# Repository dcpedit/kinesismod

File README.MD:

# Project moved to [Pillz Mod](https://github.com/dcpedit/pillzmod)

This project has been replaced by Pillz Mod: https://github.com/dcpedit/pillzmod

# Kinesis Stapelberg Mod in KiCAD

This is a fork of Aaron Silman's [kinesismod project](https://gitlab.com/Silman/kinesismod.git).  You can read more about it [on his blog](https://silman.io/project/kinesis_mod/)

This fork contains the following changes:

* Created a version that uses the Teensy 4.x
* Created a version that uses the STM32F411 Blackpill controller (`blackpill` directory)
* Use Vial firmware (`firmware` directory).
* Use ZMK firmware (`firmware` directory) wireless PillBug BLE option.

## USB Port

I recommend purchasing the following adapter from Amazon:
https://a.co/d/cRoqHqx

Here's how it looks like after installing:

## Wireless Bluetooth + ZMK
Bluetooth has been verified to work using the PillBug development board.  Below, you can see a 2000mAh 3.7V battery ([Amazon link](https://a.co/d/dVUdHxi)), as well as a 10mm push button ([Amazon link](https://a.co/d/5OVO4dY)) to disconnect the power when needed.

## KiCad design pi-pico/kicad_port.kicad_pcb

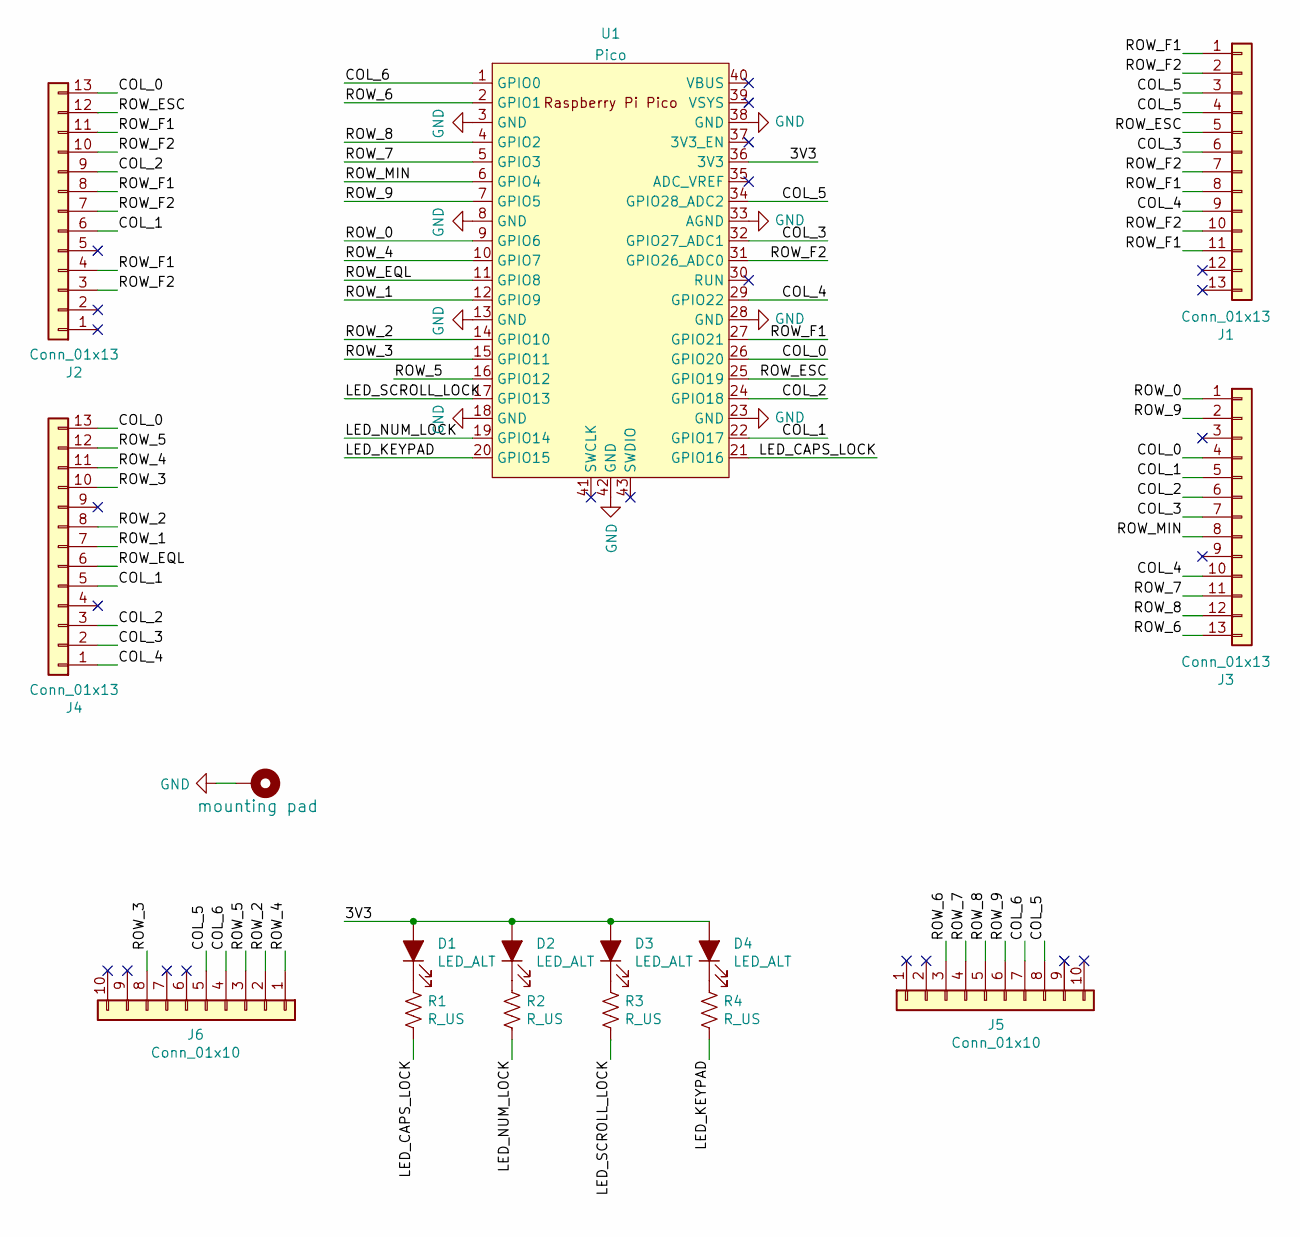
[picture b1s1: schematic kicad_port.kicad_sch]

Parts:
D1, D2, D3, D4: LED_ALT; LED_D3.0mm
H1: mounting pad; MountingHole_4.3mm_M4_Pad
J1, J2: Conn_01x13; Molex_0039532135
J3, J4: Conn_01x13; Molex_039532134
J5, J6: Conn_01x10; Pin_Header_Straight_1x10_Pitch2.54mm
R1, R2, R3, R4: R_US; R_Axial_DIN0204_L3.6mm_D1.6mm_P5.08mm_Horizontal
U1: Pico; RPi_Pico_SMD_TH

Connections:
/3V3: D1.2 (A), D2.2 (A), D3.2 (A), D4.2 (A), U1.36 (3V3)
/COL_0: J2.13, J3.4, J4.13, U1.26 (GPIO20)
/COL_1: J2.6, J3.5, J4.5, U1.22 (GPIO17)
/COL_2: J2.9, J3.6, J4.3, U1.24 (GPIO18)
/COL_3: J1.6, J3.7, J4.2, U1.32 (GPIO27_ADC1)
/COL_4: J1.9, J3.10, J4.1, U1.29 (GPIO22)
/COL_5: J1.3, J1.4, J5.8, J6.5, U1.34 (GPIO28_ADC2)
/COL_6: J5.7, J6.4, U1.1 (GPIO0)
/LED_CAPS_LOCK: R1.2, U1.21 (GPIO16)
/LED_KEYPAD: R4.2, U1.20 (GPIO15)
/LED_NUM_LOCK: R2.2, U1.19 (GPIO14)
/LED_SCROLL_LOCK: R3.2, U1.17 (GPIO13)
/ROW_0: J3.1, U1.9 (GPIO6)
/ROW_1: J4.7, U1.12 (GPIO9)
/ROW_2: J4.8, J6.2, U1.14 (GPIO10)
/ROW_3: J4.10, J6.8, U1.15 (GPIO11)
/ROW_4: J4.11, J6.1, U1.10 (GPIO7)
/ROW_5: J4.12, J6.3, U1.16 (GPIO12)
/ROW_6: J3.13, J5.3, U1.2 (GPIO1)
/ROW_7: J3.11, J5.4, U1.5 (GPIO3)
/ROW_8: J3.12, J5.5, U1.4 (GPIO2)
/ROW_9: J3.2, J5.6, U1.7 (GPIO5)
/ROW_EQL: J4.6, U1.11 (GPIO8)
/ROW_ESC: J1.5, J2.12, U1.25 (GPIO19)
/ROW_F1: J1.1, J1.8, J1.11, J2.4, J2.8, J2.11, U1.27 (GPIO21)
/ROW_F2: J1.2, J1.7, J1.10, J2.3, J2.7, J2.10, U1.31 (GPIO26_ADC0)
/ROW_MIN: J3.8, U1.6 (GPIO4)
GND: H1.1, U1.3 (GND), U1.8 (GND), U1.13 (GND), U1.18 (GND), U1.23 (GND), U1.28 (GND), U1.33 (AGND), U1.38 (GND), U1.42 (GND)
unnamed: D1.1 (K), R1.1
unnamed: D2.1 (K), R2.1
unnamed: D3.1 (K), R3.1
unnamed: D4.1 (K), R4.1

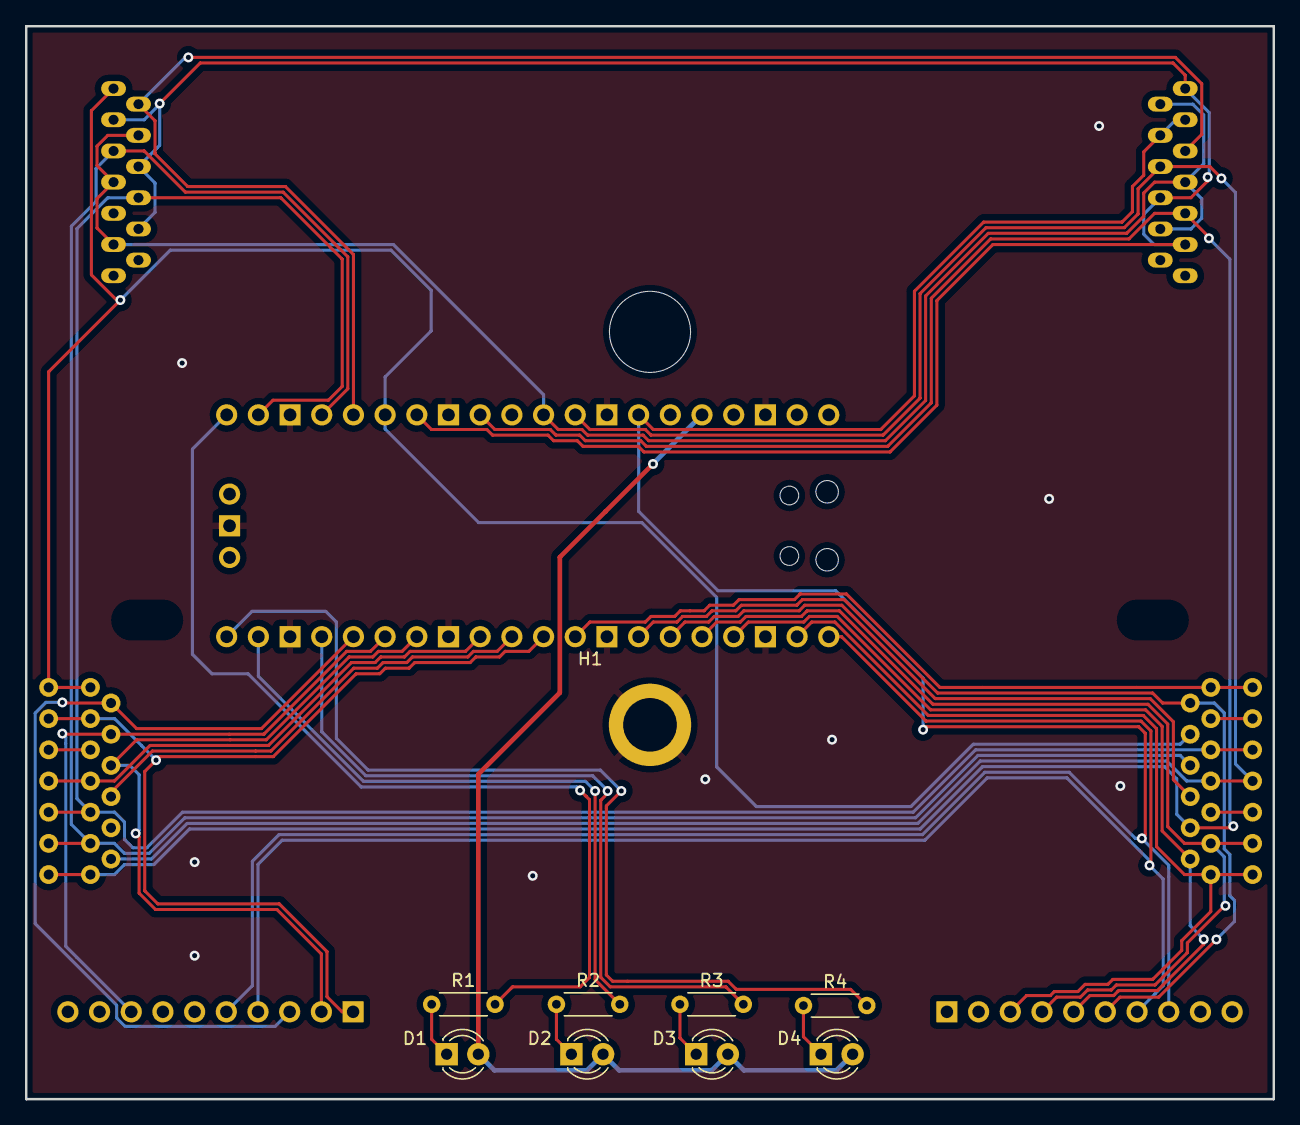
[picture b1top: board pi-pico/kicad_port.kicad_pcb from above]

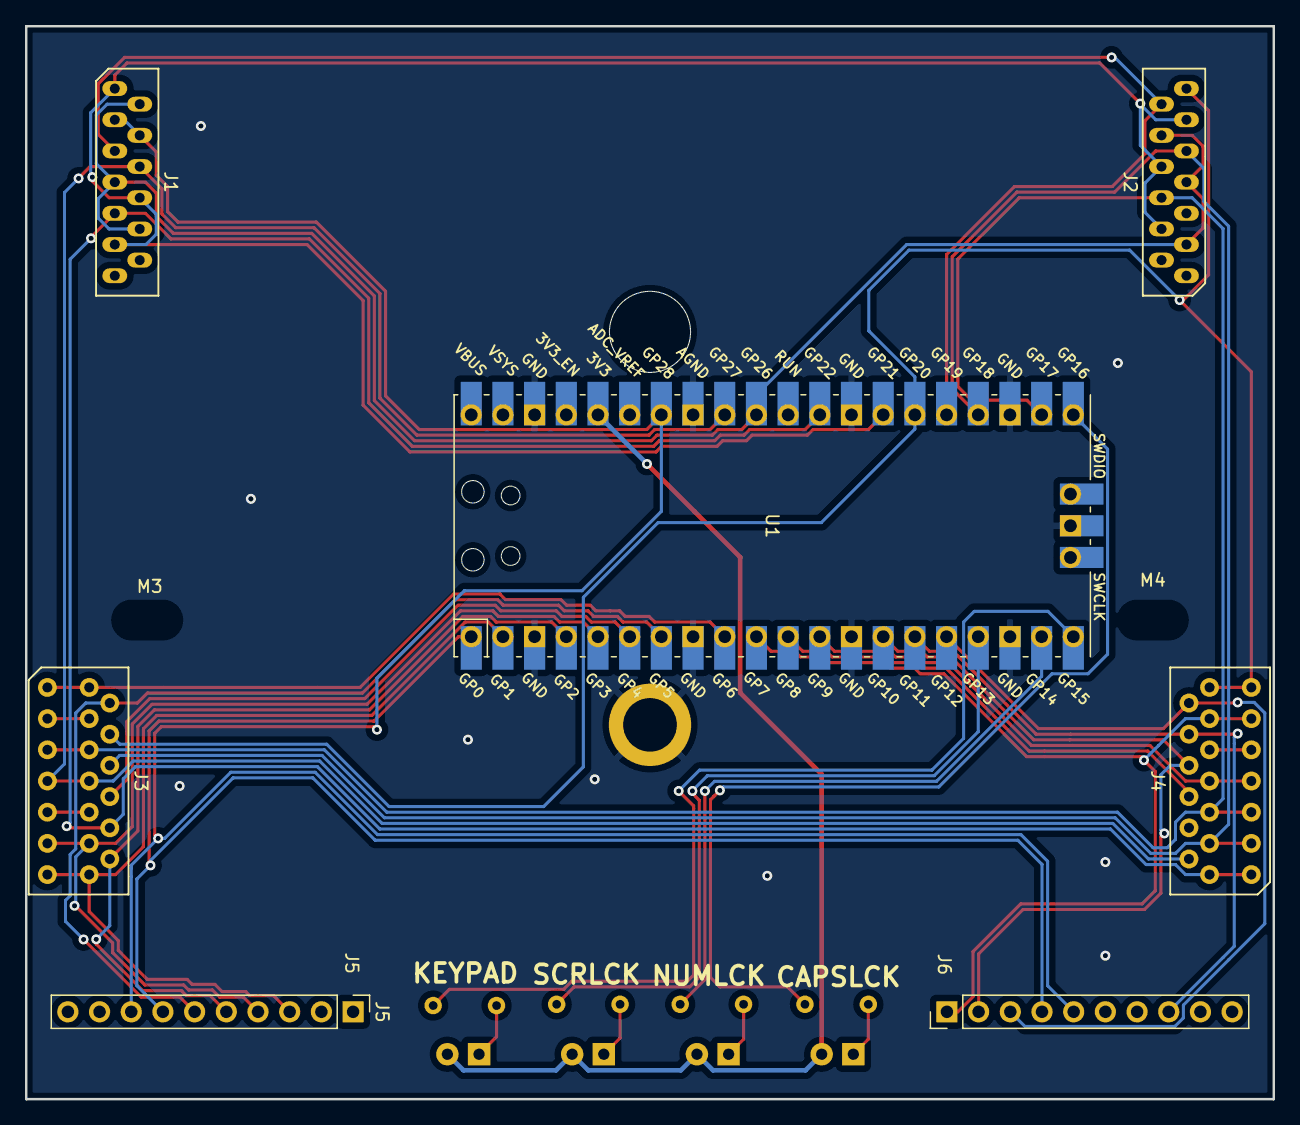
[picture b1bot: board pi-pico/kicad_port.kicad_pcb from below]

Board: 2 copper layers, 100.0 x 86.0 mm, 19 parts (10 on the bottom side), 32 nets.

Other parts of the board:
M1: MountingHole_6.4mm_M6
M3, M4: MountingHole_4.3mm_M4

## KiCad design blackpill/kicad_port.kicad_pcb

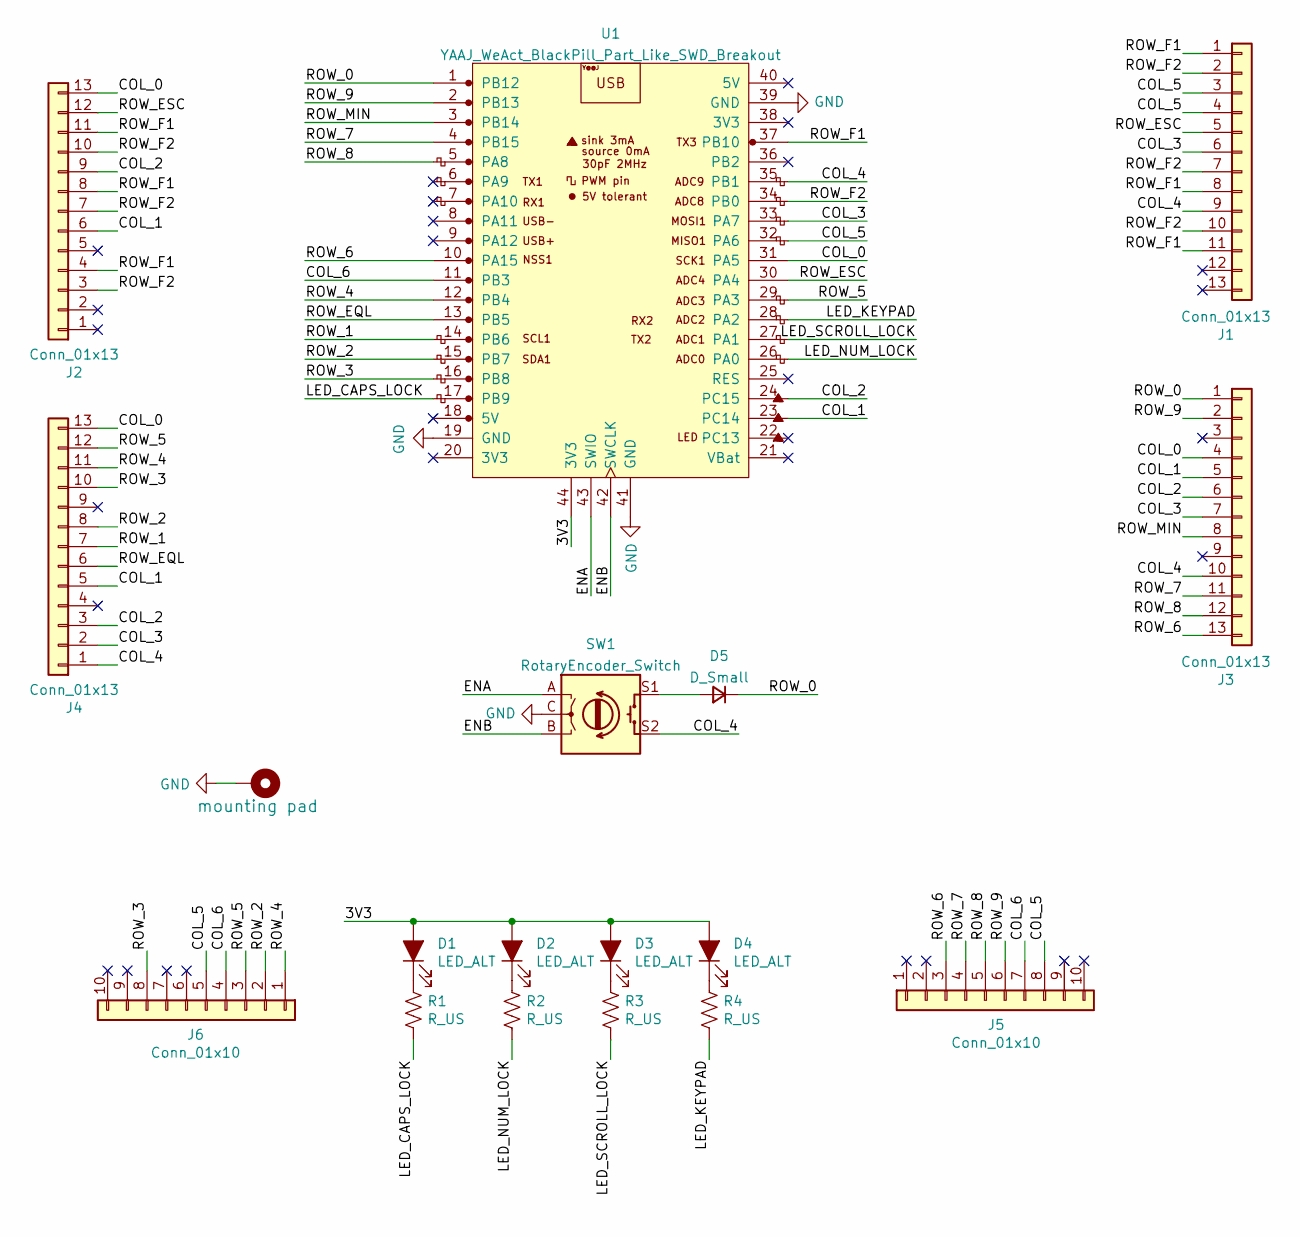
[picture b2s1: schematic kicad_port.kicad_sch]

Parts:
D1, D2, D3, D4: LED_ALT; LED_D3.0mm
D5: D_Small
H1: mounting pad; MountingHole_4.3mm_M4_Pad
J1, J2: Conn_01x13; Molex_0039532135
J3, J4: Conn_01x13; Molex_039532134
J5, J6: Conn_01x10; Pin_Header_Straight_1x10_Pitch2.54mm
R1, R2, R3, R4: R_US; R_Axial_DIN0204_L3.6mm_D1.6mm_P5.08mm_Horizontal
SW1: RotaryEncoder_Switch
U1: YAAJ_WeAct_BlackPill_Part_Like_SWD_Breakout; YAAJ_WeAct_BlackPill_SWD_2

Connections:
/3V3: D1.2 (A), D2.2 (A), D3.2 (A), D4.2 (A), U1.20 (3V3), U1.44 (3V3)
/COL_0: J2.13, J3.4, J4.13, U1.31 (PA5)
/COL_1: J2.6, J3.5, J4.5, U1.23 (PC14)
/COL_2: J2.9, J3.6, J4.3, U1.24 (PC15)
/COL_3: J1.6, J3.7, J4.2, U1.33 (PA7)
/COL_4: J1.9, J3.10, J4.1, SW1.S2, U1.35 (PB1)
/COL_5: J1.3, J1.4, J5.8, J6.5, U1.32 (PA6); also elsewhere on the board
/COL_6: J5.7, J6.4, U1.11 (PB3); also elsewhere on the board
/ENA: SW1.A, U1.43 (SWIO)
/ENB: SW1.B, U1.42 (SWCLK)
/LED_CAPS_LOCK: R1.2, U1.17 (PB9)
/LED_KEYPAD: R4.2, U1.28 (PA2)
/LED_NUM_LOCK: R2.2, U1.26 (PA0)
/LED_SCROLL_LOCK: R3.2, U1.27 (PA1)
/ROW_0: D5.1 (K), J3.1, U1.1 (PB12)
/ROW_1: J4.7, U1.14 (PB6)
/ROW_2: J4.8, J6.2, U1.15 (PB7); also elsewhere on the board
/ROW_3: J4.10, J6.8, U1.16 (PB8); also elsewhere on the board
/ROW_4: J4.11, J6.1, U1.12 (PB4); also elsewhere on the board
/ROW_5: J4.12, J6.3, U1.29 (PA3); also elsewhere on the board
/ROW_6: J3.13, J5.3, U1.10 (PA15); also elsewhere on the board
/ROW_7: J3.11, J5.4, U1.4 (PB15); also elsewhere on the board
/ROW_8: J3.12, J5.5, U1.5 (PA8); also elsewhere on the board
/ROW_9: J3.2, J5.6, U1.2 (PB13); also elsewhere on the board
/ROW_EQL: J4.6, U1.13 (PB5)
/ROW_ESC: J1.5, J2.12, U1.30 (PA4)
/ROW_F1: J1.1, J1.8, J1.11, J2.4, J2.8, J2.11, U1.37 (PB10)
/ROW_F2: J1.2, J1.7, J1.10, J2.3, J2.7, J2.10, U1.34 (PB0)
/ROW_MIN: J3.8, U1.3 (PB14)
GND: H1.1, SW1.C, U1.19 (GND), U1.39 (GND), U1.41 (GND)
unnamed: D1.1 (K), R1.1
unnamed: D2.1 (K), R2.1
unnamed: D3.1 (K), R3.1
unnamed: D4.1 (K), R4.1
unnamed: D5.2 (A), SW1.S1

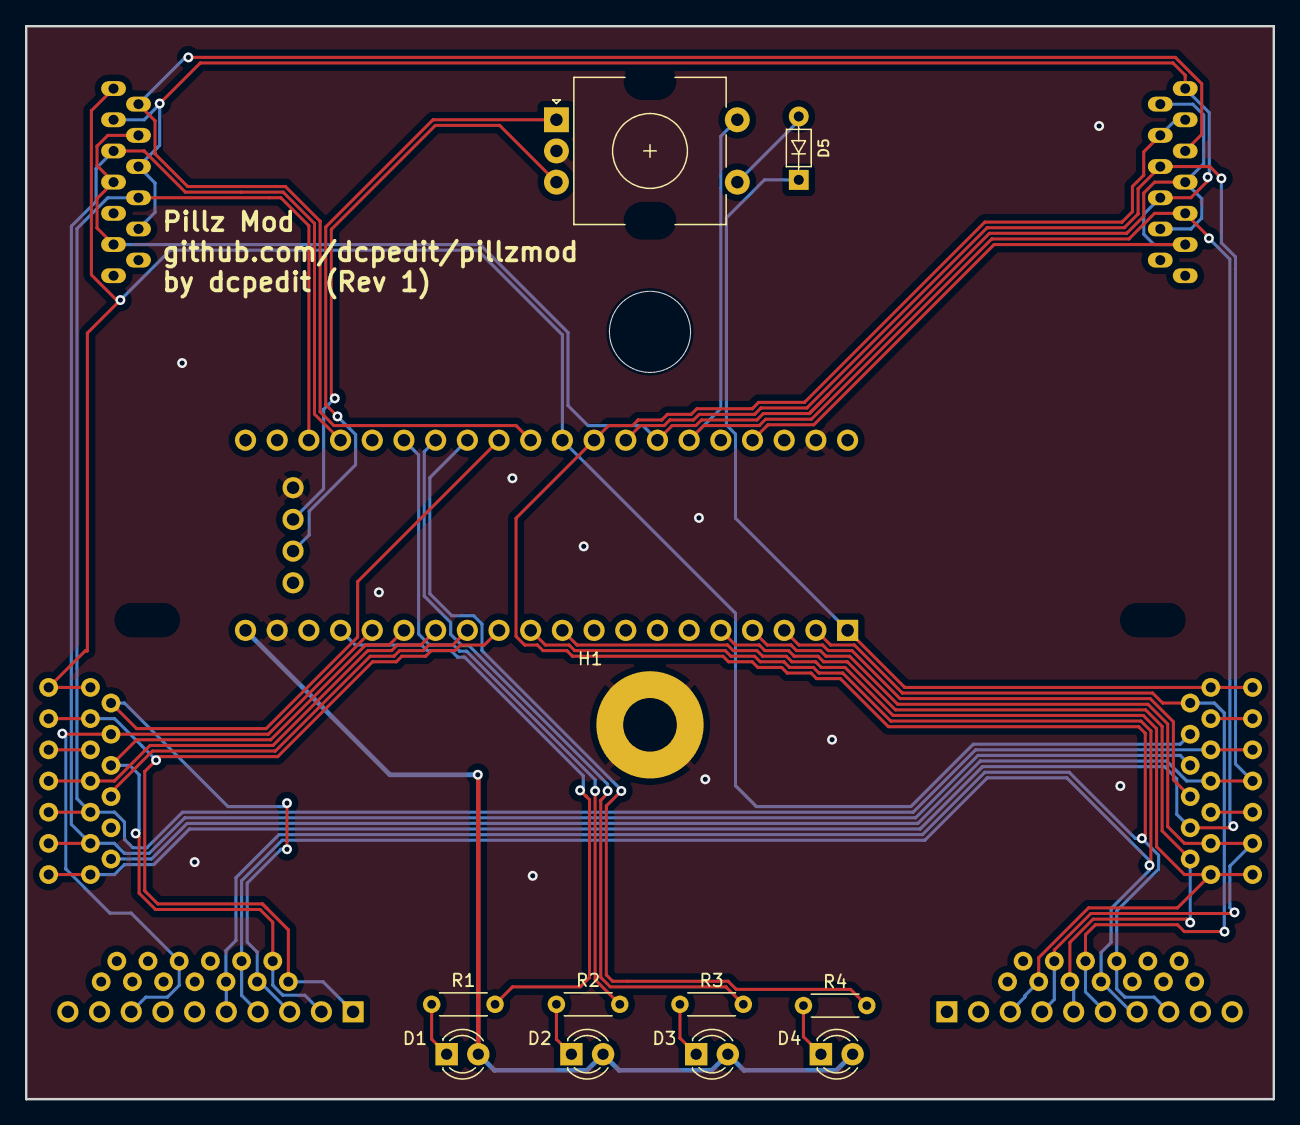
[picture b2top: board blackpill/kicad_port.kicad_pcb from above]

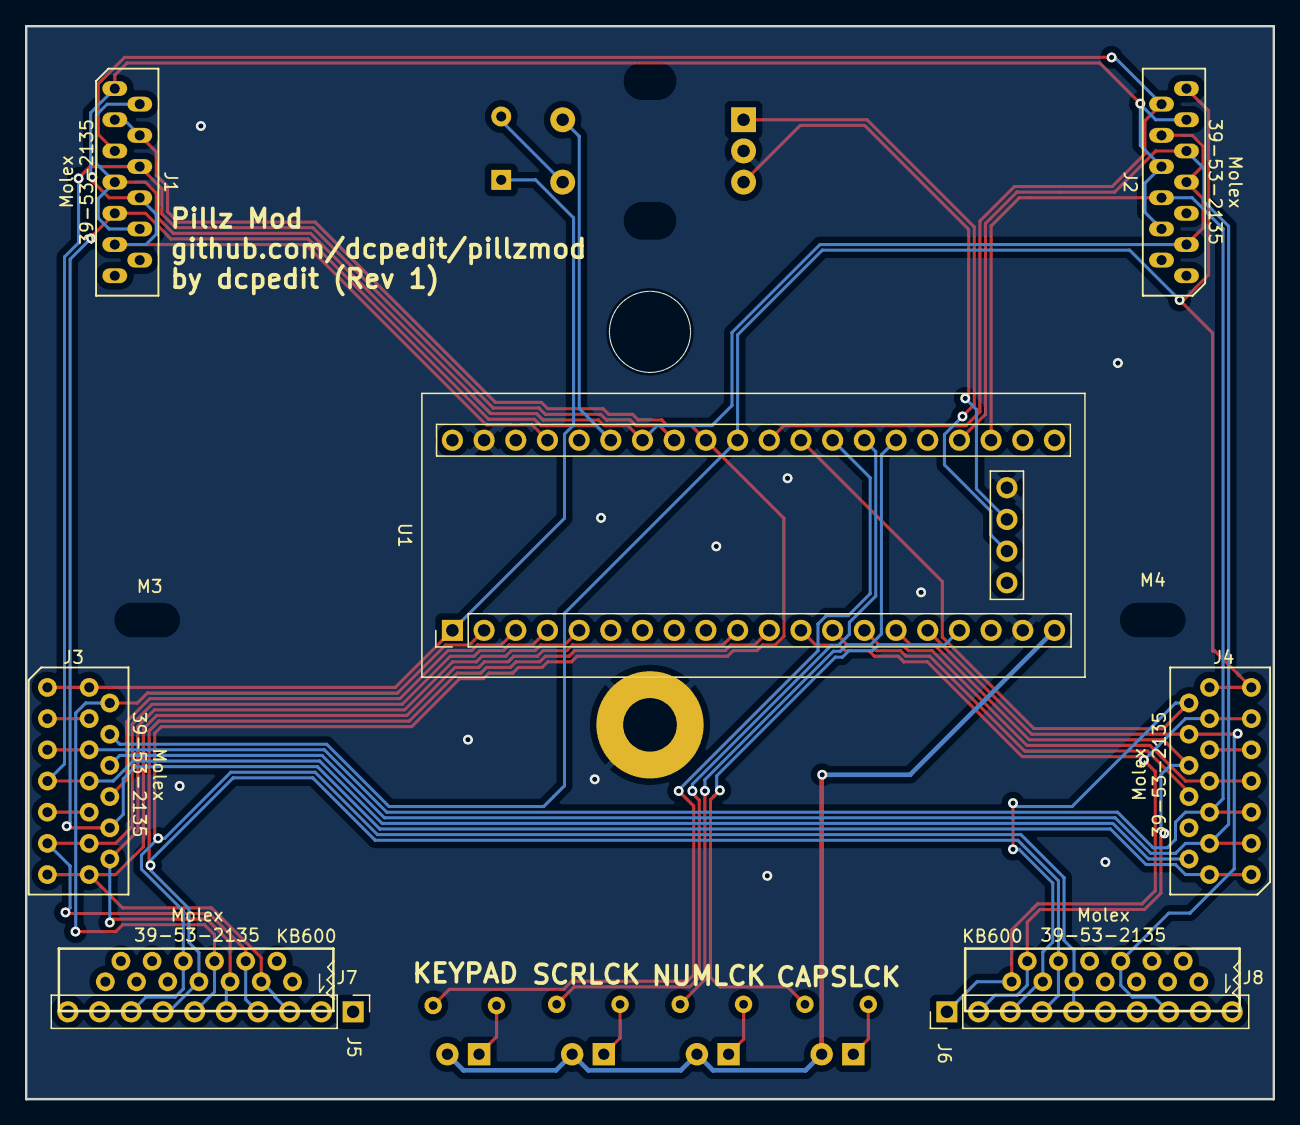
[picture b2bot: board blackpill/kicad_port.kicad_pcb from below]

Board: 2 copper layers, 100.0 x 86.0 mm, 23 parts (12 on the bottom side), 35 nets.

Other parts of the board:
J7, J8: Conn_01x13; 39-53-2135
M1: MountingHole_6.4mm_M6
M3, M4: MountingHole_4.3mm_M4

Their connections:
/COL_5: J7.8, J8.9; also elsewhere on the board
/COL_6: J7.7, J8.10; also elsewhere on the board
/ROW_2: J8.12; also elsewhere on the board
/ROW_3: J8.6; also elsewhere on the board
/ROW_4: J8.13; also elsewhere on the board
/ROW_5: J8.11; also elsewhere on the board
/ROW_6: J7.3; also elsewhere on the board
/ROW_7: J7.4; also elsewhere on the board
/ROW_8: J7.5; also elsewhere on the board
/ROW_9: J7.6; also elsewhere on the board

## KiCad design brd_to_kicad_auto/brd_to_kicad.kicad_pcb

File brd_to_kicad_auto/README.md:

# KiCAD auto-generated from brd files

I used this as a quick reference to check layout along with the original schematic images. Do not trust this as ground truth for the port.

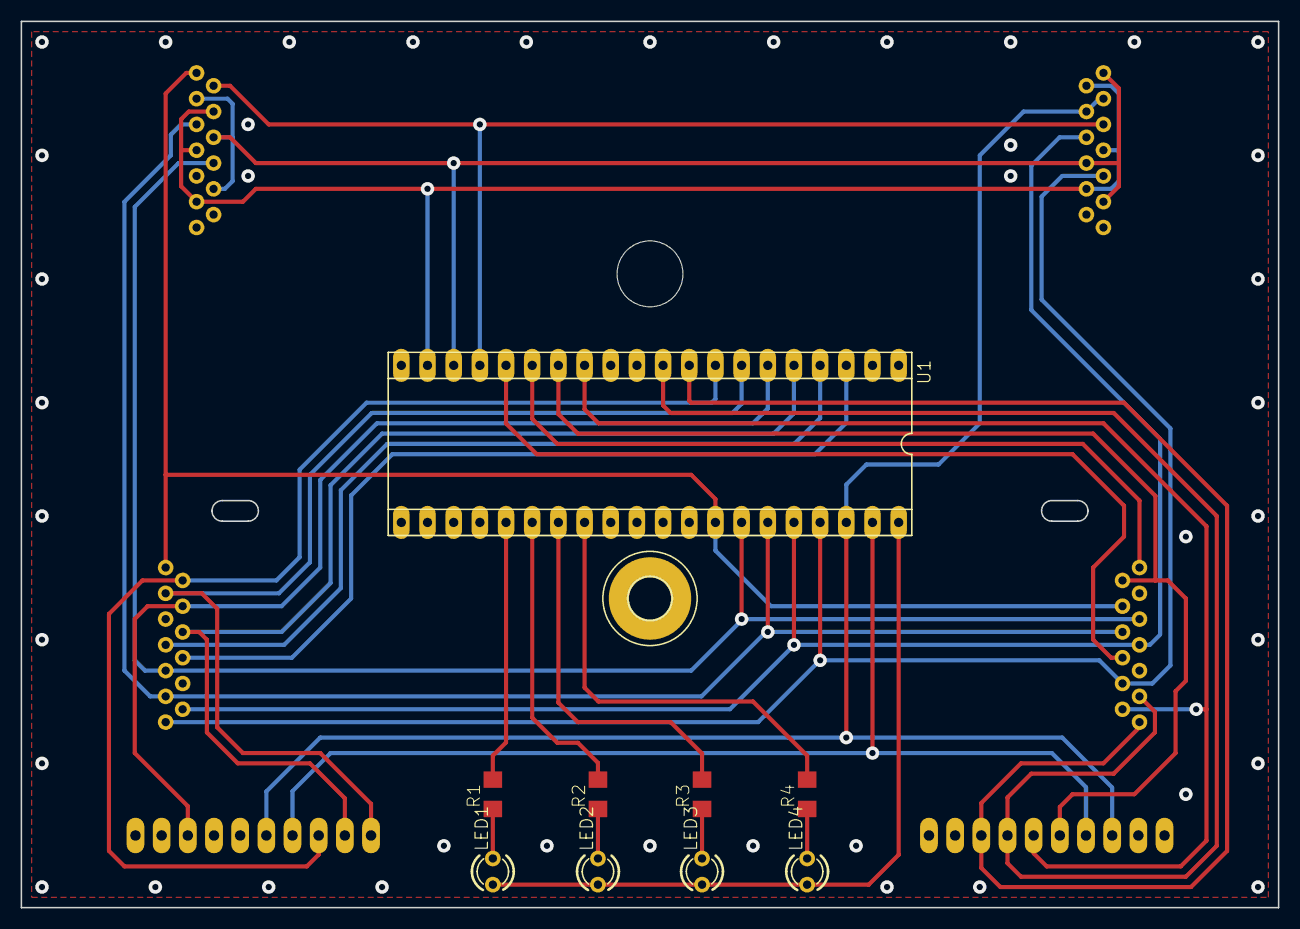
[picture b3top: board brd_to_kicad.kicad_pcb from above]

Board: 16 copper layers, 122.0 x 86.0 mm, 17 parts (0 on the bottom side), 31 nets.

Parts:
@HOLE0: (no value)
DAUMENLINKS: MA10-1
DAUMENRECHTS: MA10-1
H1: MOUNT-PAD-ROUND4.1; 4,1-PAD
LED1, LED2, LED3, LED4: LED3MM
R1, R2, R3, R4: R1206
TASTENLINKS: 39-53-2355; 39-53-2135
TASTENRECHTS: 39-53-2355; 39-53-2135
TOPLINKS: 39-53-2355; 39-53-2135
TOPRECHTS: 39-53-2355; 39-53-2135
U1: C-TEENSY++; TEENSY++

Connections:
B0: TASTENLINKS.P$1, TASTENRECHTS.P$10, TOPLINKS.P$1, U1.B0
B1: TASTENLINKS.P$9, TASTENRECHTS.P$9, TOPLINKS.P$8, U1.B1
B2: TASTENLINKS.P$11, TASTENRECHTS.P$8, TOPLINKS.P$5, U1.B2
B3: TASTENLINKS.P$12, TASTENRECHTS.P$7, TOPRECHTS.P$8, U1.B3
B4: TASTENLINKS.P$13, TASTENRECHTS.P$4, TOPRECHTS.P$5, U1.B4
B5: DAUMENLINKS.8, DAUMENRECHTS.5, TOPRECHTS.P$10, TOPRECHTS.P$11, U1.B5
B6: DAUMENLINKS.7, DAUMENRECHTS.4, U1.B6
C0: DAUMENLINKS.5, TASTENRECHTS.P$2, U1.C0
C1: DAUMENLINKS.6, TASTENRECHTS.P$12, U1.C1
C2: TASTENRECHTS.P$13, U1.C2
C3: TASTENRECHTS.P$6, U1.C3
C4: TOPLINKS.P$2, TOPRECHTS.P$9, U1.C4
C5: TOPLINKS.P$3, TOPLINKS.P$6, TOPLINKS.P$10, TOPRECHTS.P$3, TOPRECHTS.P$6, TOPRECHTS.P$13, U1.C5
C6: TOPLINKS.P$4, TOPLINKS.P$7, TOPLINKS.P$11, TOPRECHTS.P$4, TOPRECHTS.P$7, TOPRECHTS.P$12, U1.C6
D0: TASTENLINKS.P$8, U1.D0
D1: TASTENLINKS.P$7, U1.D1
D2: DAUMENRECHTS.2, TASTENLINKS.P$6, U1.D2
D3: DAUMENRECHTS.8, TASTENLINKS.P$4, U1.D3
D4: DAUMENRECHTS.1, TASTENLINKS.P$3, U1.D4
D5: DAUMENRECHTS.3, TASTENLINKS.P$2, U1.D5
D6: DAUMENLINKS.3, TASTENRECHTS.P$1, U1.D6
D7: DAUMENLINKS.4, TASTENRECHTS.P$3, U1.D7
unnamed: R1.2, U1.F3
unnamed: R2.2, U1.F2
unnamed: R3.2, U1.F1
unnamed: R4.2, U1.F0
unnamed: LED1.A, LED2.A, LED3.A, LED4.A, U1.+5V
unnamed: LED4.K, R4.1
unnamed: LED3.K, R3.1
unnamed: LED2.K, R2.1
unnamed: LED1.K, R1.1

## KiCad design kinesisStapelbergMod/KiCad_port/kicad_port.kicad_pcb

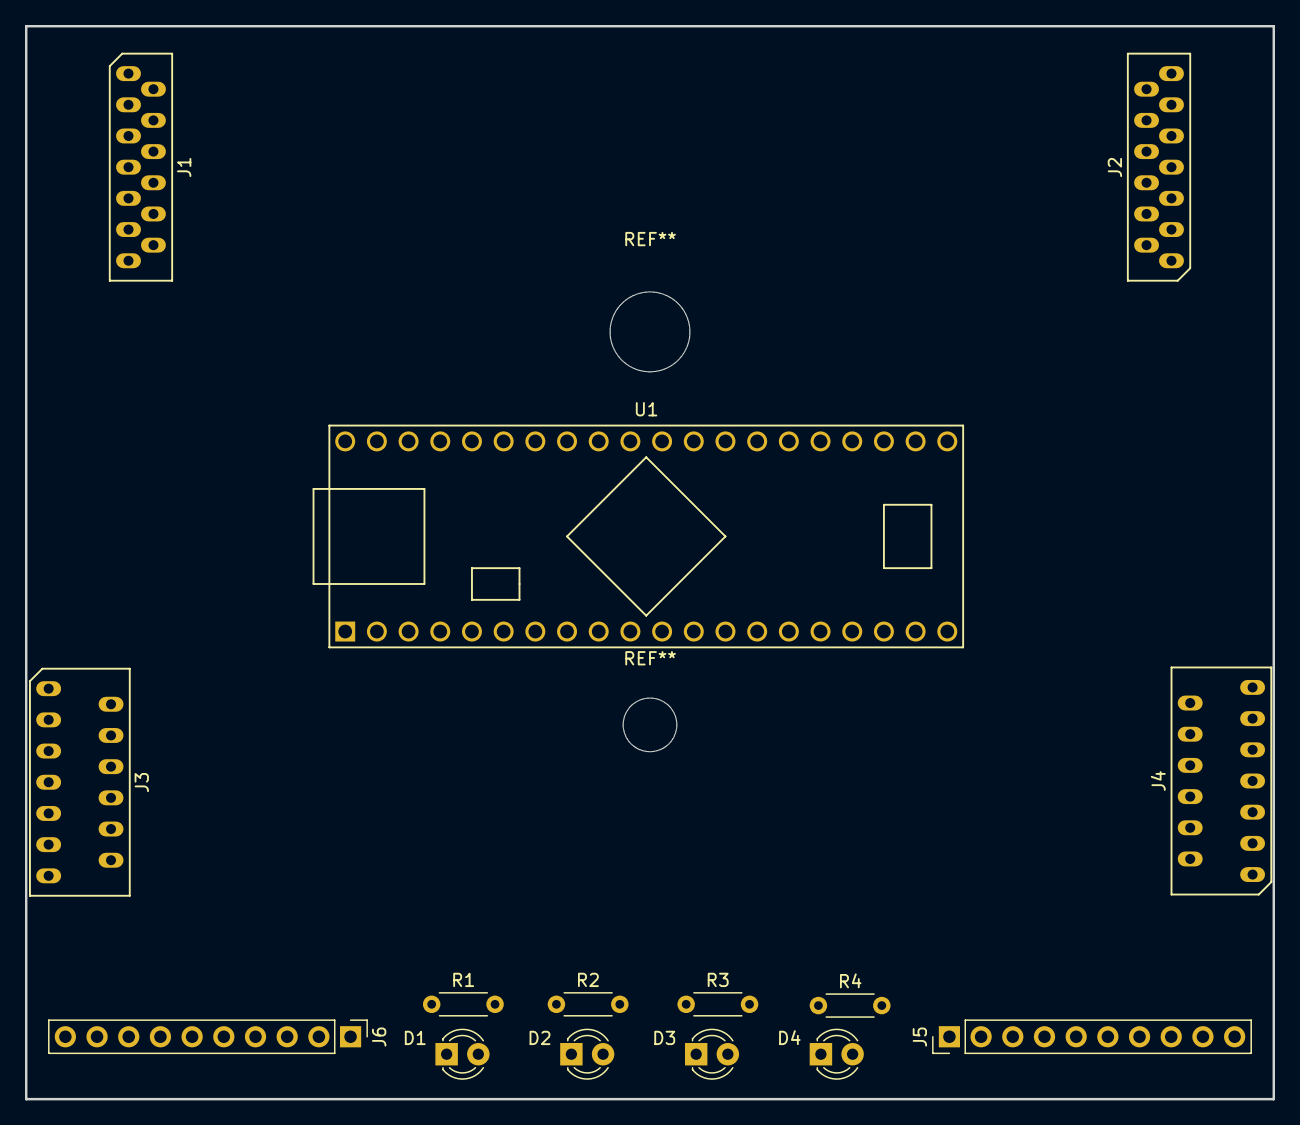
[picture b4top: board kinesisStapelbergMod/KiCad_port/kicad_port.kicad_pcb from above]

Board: 2 copper layers, 100.0 x 86.0 mm, 15 parts (0 on the bottom side), 32 nets, no tracks yet.

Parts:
D1, D2, D3, D4: LED_ALT; LED_D3.0mm
J1, J2: Conn_01x13; Molex_0039532135
J3, J4: Conn_01x13; Molex_039532134
J5, J6: Conn_01x10; Pin_Header_Straight_1x10_Pitch2.54mm
R1, R2, R3, R4: R_US; R_Axial_DIN0204_L3.6mm_D1.6mm_P5.08mm_Horizontal
U1: Teensy++_2_0; Teensy++_2_0_40p

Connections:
+5V: D1.2, D2.2, D3.2, D4.2, U1.21
/PB0: J2.1, J3.10, J4.1, U1.28
/PB1: J2.8, J3.9, J4.9, U1.27
/PB2: J2.5, J3.8, J4.11, U1.26
/PB3: J1.8, J3.7, J4.12, U1.25
/PB4: J1.5, J3.4, J4.13, U1.24
/PB5: J1.10, J1.11, J5.8, J6.5, U1.23
/PB6: J5.7, J6.4, U1.22
/PC0: J3.2, J5.5, U1.13
/PC1: J3.12, J5.6, U1.14
/PC2: J3.13, U1.15
/PC3: J3.6, U1.16
/PC4: J1.9, J2.2, U1.17
/PC5: J1.3, J1.6, J1.13, J2.3, J2.6, J2.10, U1.18
/PC6: J1.4, J1.7, J1.12, J2.4, J2.7, J2.11, U1.19
/PD0: J4.8, U1.3
/PD1: J4.7, U1.4
/PD2: J4.6, J6.2, U1.5
/PD3: J4.4, J6.8, U1.6
/PD4: J4.3, J6.1, U1.7
/PD5: J4.2, J6.3, U1.8
/PD6: J3.1, J5.3, U1.9
/PD7: J3.3, J5.4, U1.10
/PF0: R4.2, U1.33
/PF1: R3.2, U1.34
/PF2: R2.2, U1.35
/PF3: R1.2, U1.36
GND: U1.1, U1.31
unnamed: D1.1, R1.1
unnamed: D2.1, R2.1
unnamed: D3.1, R3.1
unnamed: D4.1, R4.1

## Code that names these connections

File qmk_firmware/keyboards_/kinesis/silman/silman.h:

#ifndef KINESIS_SILMAN_H
#define KINESIS_SILMAN_H

#include "quantum.h"

#define ___ KC_NO

// This a shortcut to help you visually see your layout.
// The first section contains all of the arguments as on the physical keyboard
// The second converts the arguments into the 2-D scanned array

#define LAYOUT(                                   \
    kC0, kD0, kE0, kC1, kD1, kE1, kC2, kD2, kE2,  \
    k00, k10, k20, k30, k40, k50,                 \
    k01, k11, k21, k31, k41, k51,                 \
    k02, k12, k22, k32, k42, k52,                 \
    k03, k13, k23, k33, k43, k53,                 \
         k14, k24, k34, k54,                      \
                             k56, k55,            \
                                  k35,            \
                        k36, k46, k25,            \
                                                  \
    kC3, kD3, kE3, kC4, kD4, kE4, kC5, kE5, kD5,  \
                   k60, k70, k80, k90, kA0, kB0,  \
                   k61, k71, k81, k91, kA1, kB1,  \
                   k62, k72, k82, k92, kA2, kB2,  \
                   k63, k73, k83, k93, kA3, kB3,  \
                        k64, k84, k94, kA4,       \
              k96, k85,                           \
              k86,                                \
              k66, k75, k65                       \
) {                                              \
    { k00,  k01,  k02,  k03,  ___,  ___,  ___ }, \
    { k10,  k11,  k12,  k13,  k14,  ___,  ___ }, \
    { k20,  k21,  k22,  k23,  k24,  k25,  ___ }, \
    { k30,  k31,  k32,  k33,  k34,  k35,  k36 }, \
    { k40,  k41,  k42,  k43,  ___,  ___,  k46 }, \
    { k50,  k51,  k52,  k53,  k54,  k55,  k56 }, \
    { k60,  k61,  k62,  k63,  k64,  k65,  k66 }, \
    { k70,  k71,  k72,  k73,  ___,  k75,  ___ }, \
    { k80,  k81,  k82,  k83,  k84,  k85,  k86 }, \
    { k90,  k91,  k92,  k93,  k94,  ___,  k96 }, \
    { kA0,  kA1,  kA2,  kA3,  kA4,  ___,  ___ }, \
    { kB0,  kB1,  kB2,  kB3,  ___,  ___,  ___ }, \
    { kC0,  kC1,  kC2,  kC3,  kC4,  kC5,  ___ }, \
    { kD0,  kD1,  kD2,  kD3,  kD4,  kD5,  ___ }, \
    { kE0,  kE1,  kE2,  kE3,  kE4,  kE5,  ___ } \
}

/*  ---------------- LEFT HAND -----------------   ---------------- RIGHT HAND ---------------- */
#define LAYOUT_pretty(                                                                           \
    kC0, kD0, kE0, kC1, kD1, kE1, kC2, kD2, kE2,   kC3, kD3, kE3, kC4, kD4, kE4, kC5, kE5, kD5,  \
    k00, k10, k20, k30, k40, k50,                            k60, k70, k80, k90, kA0, kB0,       \
    k01, k11, k21, k31, k41, k51,                            k61, k71, k81, k91, kA1, kB1,       \
    k02, k12, k22, k32, k42, k52,                            k62, k72, k82, k92, kA2, kB2,       \
    k03, k13, k23, k33, k43, k53,                            k63, k73, k83, k93, kA3, kB3,       \
         k14, k24, k34, k54,                                      k64, k84, k94, kA4,            \
                             k56, k55,                  k96, k85,                                \
                                  k35,                  k86,                                     \
                        k36, k46, k25,                  k66, k75, k65                            \
) {                                              \
    { k00,  k01,  k02,  k03,  ___,  ___,  ___ }, \
    { k10,  k11,  k12,  k13,  k14,  ___,  ___ }, \
    { k20,  k21,  k22,  k23,  k24,  k25,  ___ }, \
    { k30,  k31,  k32,  k33,  k34,  k35,  k36 }, \
    { k40,  k41,  k42,  k43,  ___,  ___,  k46 }, \
    { k50,  k51,  k52,  k53,  k54,  k55,  k56 }, \
    { k60,  k61,  k62,  k63,  k64,  k65,  k66 }, \
    { k70,  k71,  k72,  k73,  ___,  k75,  ___ }, \
    { k80,  k81,  k82,  k83,  k84,  k85,  k86 }, \
    { k90,  k91,  k92,  k93,  k94,  ___,  k96 }, \
    { kA0,  kA1,  kA2,  kA3,  kA4,  ___,  ___ }, \
    { kB0,  kB1,  kB2,  kB3,  ___,  ___,  ___ }, \
    { kC0,  kC1,  kC2,  kC3,  kC4,  kC5,  ___ }, \
    { kD0,  kD1,  kD2,  kD3,  kD4,  kD5,  ___ }, \
    { kE0,  kE1,  kE2,  kE3,  kE4,  kE5,  ___ }  \
}

/*
This is the Stapelberg matrix as published at
https://github.com/stapelberg/kinesis-firmware/blob/master/kb_kinesis/config.kspec
Along with the pins for each row and column
             PB0 PB1 PB2 PB3 PB4 PB5 PB6
             kx0 kx1 kx2 kx3 kx4 kx5 kx6
PD0 k0x Row: EQL TAB CAP LSH X2  --  --
PD1 k1x Row: 1   Q   A   Z   BQ  --  --
PD2 k2x Row: 2   W   S   X   INS END --
PD3 k3x Row: 3   E   D   C   LFT HOM BAK
PD4 k4x Row: 4   R   F   V   --  --  DEL
PD5 k5x Row: 5   T   G   B   RT  LAL LCT
PD6 k6x Row: 6   Y   H   N   UP  SPC PGD
PD7 k7x Row: 7   U   J   M   --  RET --
PC0 k8x Row: 8   I   K   COM DWN RCT PGU
PC1 k9x Row: 9   O   L   PER LBR --  RAL
PC2 kAx Row: 0   P   SEM SLA RBR --  --
PC3 kBx Row: MIN BSL APO RSH X1  --  --
PC4 kCx Row: ESC F3  F6  F9  F12 PAU --
PC5 kDx Row: F1  F4  F7  F10 PRT PRG --
PC6 kEx Row: F2  F5  F8  F11 SLK KEY --
*/



#endif

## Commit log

2019-02-18 initial commit, schematic done, custom molex and teensy footprints done
2019-02-18 layout begun
2019-02-19 change LED and Resistor footprints
2019-02-19 modify led position
2019-02-19 add dimensions to converted board, transferred to ported board
2019-02-21 add FreeCAD board model
2019-02-21 change dimensions alignment
2019-02-21 refactor folder locations
2019-02-25 first pass auto-routed with FreeRouting.jar, should probably re-orient some stuff (LEDS) and do another pass. Board has been 3D printed and checked for size compatibility with case and keywells
2019-02-25 re-routed with LEDs flipped onto other side of board
2019-02-25 realized J1 and J2 were swapped and J3 and J4 were swapped. Replced and re-routed
2019-02-25 parts were not on correct side of board, had to re-orient and re-route. In addition I added the 3d Models for the other parts
2019-02-25 add labels for LEDs
2019-02-26 add actual 10-pin header model and moved parts over so they arent hanging off board, re-routed
2019-02-26 slight board edit and double checking all pins. Should be good to send to fab after adding more Silk
2019-02-27 re-placed F-row connectors closer to edge, re-routed
2019-02-28 sent board files to fab
2019-07-18 add detail to README and add warning REAME to the auto generated kiCAD
2020-07-14 add usb mount model to repo
2020-11-17 remove brd_to_kicad folder, add my own qmk firmware keymap
2020-11-20 fix keymap ASCII
2020-11-20 fix more ascii
2020-11-20 fix even more ASCII
2022-07-26 Modify to support Teensy 4.x
2022-08-14 Add blackpill edition
2022-08-14 Add promicro support
2022-08-22 File cleanup
2022-08-22 Update readme. Firmware bin
2022-08-22 Add Promicro
2022-08-23 File for acrylic plate
2022-08-24 Fix typo
2022-08-25 Add Advantage compatibility
2023-11-03 Update README.MD source link
2023-12-13 Update readme with wireless info
2023-12-13 Merged changes
2023-12-13 Remove promicro dev
2023-12-13 Discontinued dev: promicro, pi-pico
2023-12-13 Remove old firmware
2024-04-12 Pillz Mod update
2024-04-12 Fix link
